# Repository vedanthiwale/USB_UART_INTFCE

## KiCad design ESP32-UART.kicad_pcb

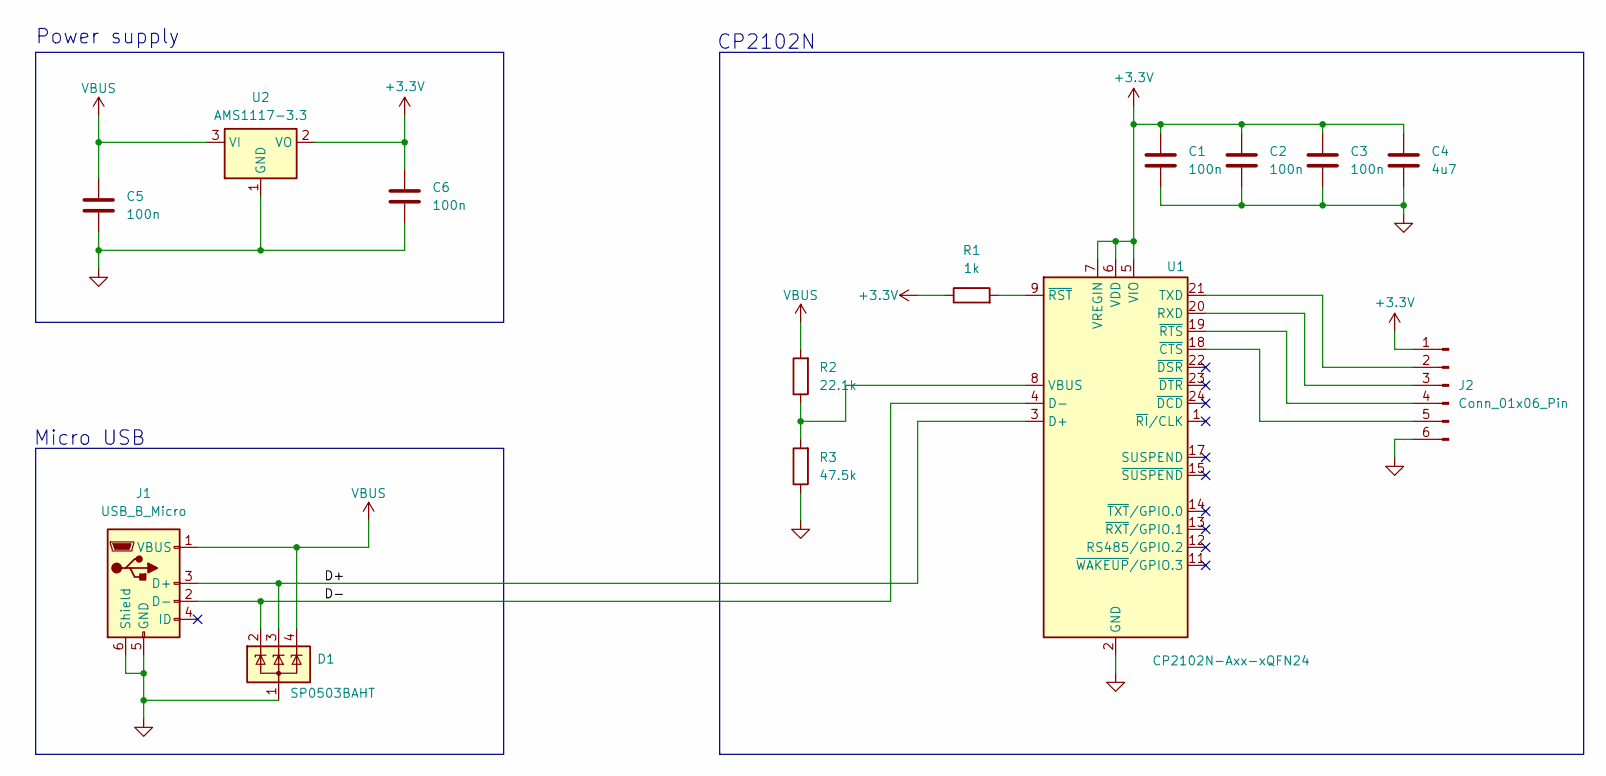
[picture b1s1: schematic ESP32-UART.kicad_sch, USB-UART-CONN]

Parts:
C1, C2, C3, C5, C6: 100n; C_0402_1005Metric
C4: 4u7; C_0402_1005Metric
D1: SP0503BAHT; SOT-143
J1: USB_B_Micro; USB_Micro-B_Molex_47346-0001
J2: Conn_01x06_Pin; PinHeader_1x06_P2.54mm_Vertical
R1: 1k; R_0402_1005Metric
R2: 22.1k; R_0402_1005Metric
R3: 47.5k; R_0402_1005Metric
U1: CP2102N-Axx-xQFN24; QFN-24-1EP_4x4mm_P0.5mm_EP2.6x2.6mm
U2: AMS1117-3.3; SOT-223-3_TabPin2

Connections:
+3.3V: C1.1, C2.1, C3.1, C4.1, C6.1, J2.1, R1.1, U1.5 (VIO), U1.6 (VDD), U1.7 (VREGIN), U2.2 (VO)
/D+: D1.3 (K), J1.3 (D+), U1.3 (D+)
/D-: D1.2 (K), J1.2 (D-), U1.4 (D-)
GND: C1.2, C2.2, C3.2, C4.2, C5.2, C6.2, D1.1 (A), J1.5 (GND), J1.6 (Shield), J2.6, R3.1, U1.2 (GND), U1.25 (GND), U2.1 (GND)
unnamed: J2.2, U1.21 (TXD)
unnamed: J2.3, U1.20 (RXD)
unnamed: J2.4, U1.19 (~RTS)
unnamed: J2.5, U1.18 (~CTS)
unnamed: R2.1, R3.2, U1.8 (VBUS)
unnamed: R1.2, U1.9 (~RST)
VBUS: C5.1, D1.4 (K), J1.1 (VBUS), R2.2, U2.3 (VI)

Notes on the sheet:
Power supply
CP2102N
Micro USB

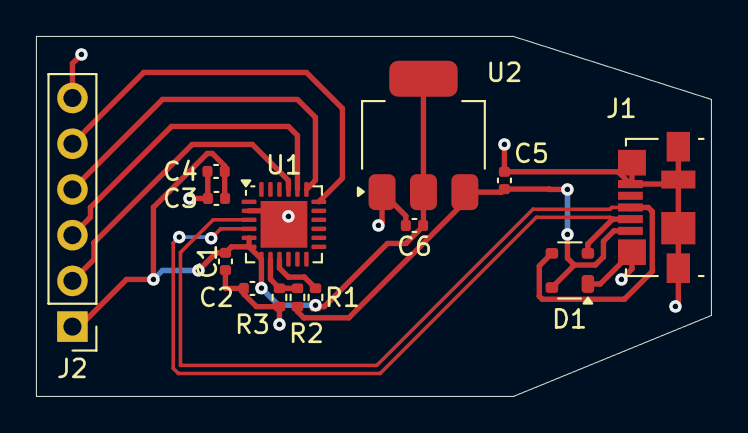
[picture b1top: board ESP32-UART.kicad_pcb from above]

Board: 2 copper layers, 37.5 x 20.0 mm, 14 parts (0 on the bottom side), 11 nets.

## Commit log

2024-12-30 30dec
